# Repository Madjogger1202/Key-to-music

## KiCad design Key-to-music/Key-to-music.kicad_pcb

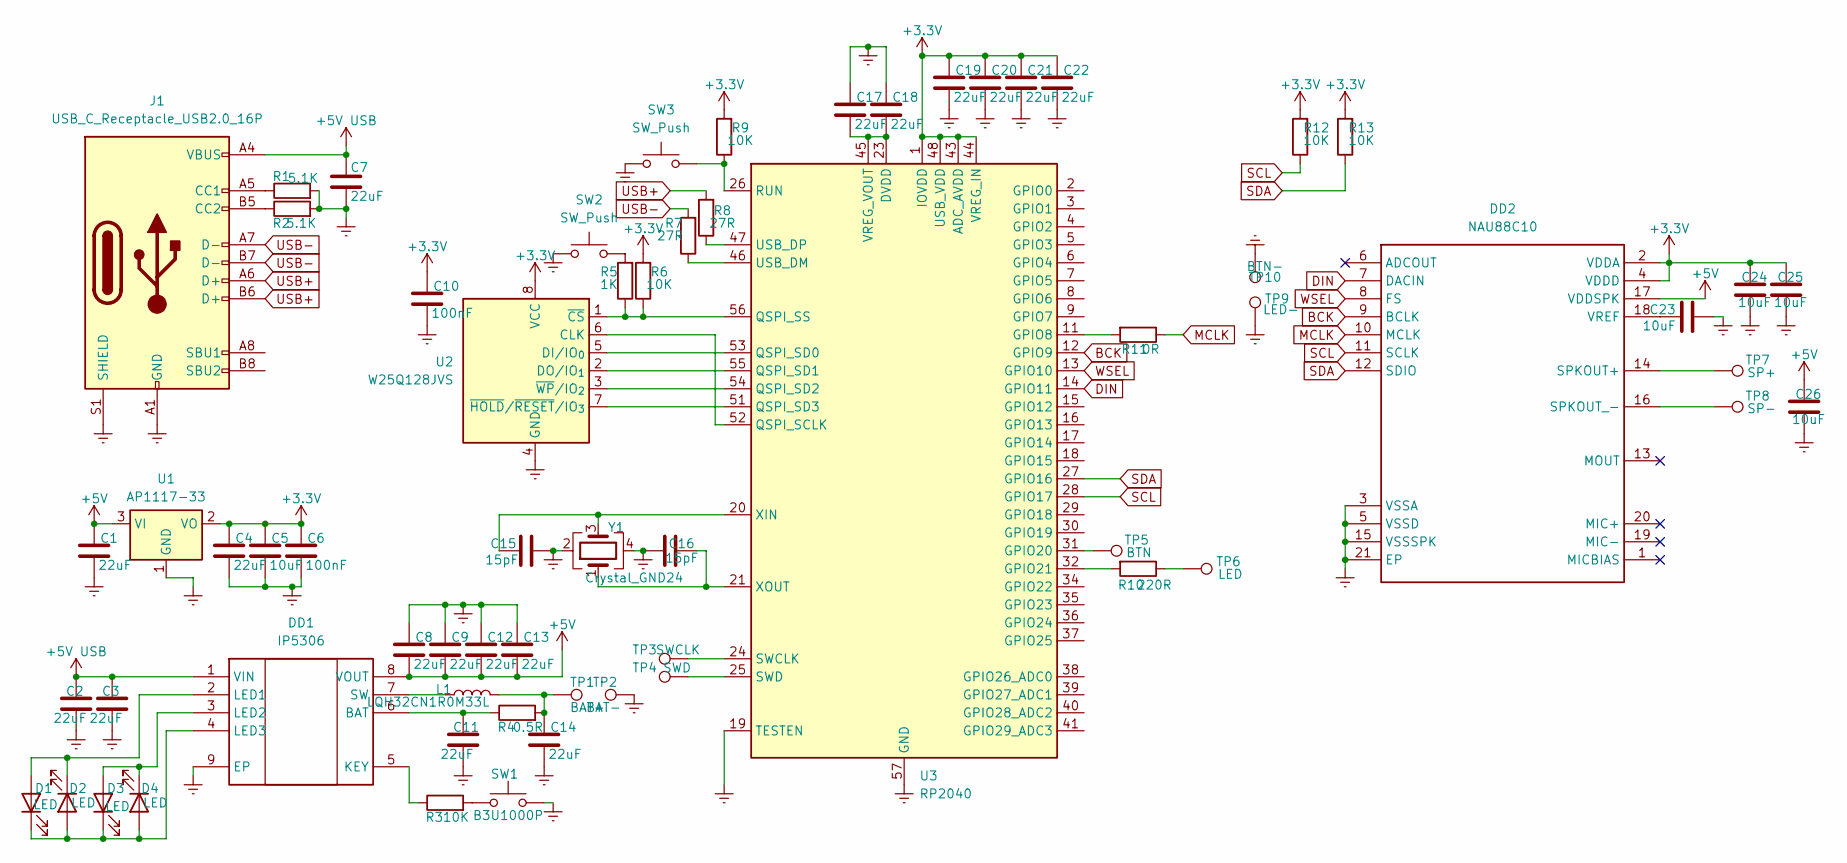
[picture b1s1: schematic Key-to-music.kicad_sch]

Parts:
C1, C2, C3, C4, C7, C8, C9, C11, C12, C13, C14, C17, C18, C19, C20, C21, C22: 22uF; C_0402_1005Metric
C5, C23, C24, C25, C26: 10uF; C_0402_1005Metric
C6, C10: 100nF; C_0402_1005Metric
C15, C16: 15pF; C_0402_1005Metric
D1, D2, D3, D4: LED; LED_0402_1005Metric
DD1: IP5306; HSOP-8-1EP_3.9x4.9mm_P1.27mm_EP2.3x2.3mm; Manufacturer_Part_Number IP5306
DD2: NAU88C10; QFN50P400X400X80-21N; Manufacturer_Part_Number NAU88C10
J1: USB_C_Receptacle_USB2.0_16P; USB_C_Receptacle_GCT_USB4105-xx-A_16P_TopMnt_Horizontal
L1: LQH32CN1R0M33L; L_1210_3225Metric
R1, R2: 5.1K; R_0402_1005Metric
R3, R6, R9, R12, R13: 10K; R_0402_1005Metric
R4: 0.5R; R_0402_1005Metric
R5: 1K; R_0402_1005Metric
R7, R8: 27R; R_0402_1005Metric
R10: 220R; R_0402_1005Metric
R11: 0R; R_0402_1005Metric
SW1: B3U1000P; SW_SPST_B3U-1000P
SW2, SW3: SW_Push; SW_SPST_B3U-1000P
TP1: BAT+; TestPoint_Pad_D2.0mm
TP2: BAT-; TestPoint_Pad_D2.0mm
TP3: SWCLK; TestPoint_Pad_D1.0mm
TP4: SWD; TestPoint_Pad_D1.0mm
TP5: BTN; TestPoint_Pad_D1.0mm
TP6: LED; TestPoint_Pad_D1.0mm
TP7: SP+; TestPoint_Pad_D1.0mm
TP8: SP-; TestPoint_Pad_D1.0mm
TP9: LED-; TestPoint_Pad_D1.0mm
TP10: BTN-; TestPoint_Pad_D1.0mm
U1: AP1117-33; SOT-223-3_TabPin2
U2: W25Q128JVS; SOIC-8_5.3x5.3mm_P1.27mm
U3: RP2040; QFN-56-1EP_7x7mm_P0.4mm_EP3.2x3.2mm
Y1: Crystal_GND24; Crystal_SMD_Abracon_ABM8G-4Pin_3.2x2.5mm

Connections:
+3.3V: C4.1, C5.1, C6.1, C10.1, C19.1, C20.1, C21.1, C22.1, C24.2, C25.2, DD2.2 (VDDA), DD2.4 (VDDD), R6.2, R9.2, R12.2, R13.2, U1.2 (VO), U2.8 (VCC), U3.1 (IOVDD), U3.10 (IOVDD), U3.22 (IOVDD), U3.33 (IOVDD), U3.42 (IOVDD), U3.43 (ADC_AVDD), U3.44 (VREG_IN), U3.48 (USB_VDD), U3.49 (IOVDD)
+5V: C1.1, C8.2, C9.2, C12.2, C13.2, C26.2, DD1.8 (VOUT), DD2.17 (VDDSPK), U1.3 (VI)
+5V USB: C2.1, C3.1, C7.1, DD1.1 (VIN), J1.A4 (VBUS), J1.A9 (VBUS), J1.B4 (VBUS), J1.B9 (VBUS)
BCK: DD2.9 (BCLK), U3.12 (GPIO9)
DIN: DD2.7 (DACIN), U3.14 (GPIO11)
Earth: C1.2, C2.2, C3.2, C4.2, C5.2, C6.2, C7.2, C8.1, C9.1, C10.2, C11.2, C12.1, C13.1, C14.2, C15.2, C16.1, C17.1, C18.1, C19.2, C20.2, C21.2, C22.2, C23.2, C24.1, C25.1, C26.1, DD1.9 (EP), DD2.3 (VSSA), DD2.5 (VSSD), DD2.15 (VSSSPK), DD2.21 (EP), J1.A1 (GND), J1.A12 (GND), J1.B1 (GND), J1.B12 (GND), J1.S1 (SHIELD), R1.2, R2.2, SW1.2, SW2.1, SW3.1, TP2.1, TP9.1, TP10.1, U1.1 (GND), U2.4 (GND), U3.19 (TESTEN), U3.57 (GND), Y1.2, Y1.4
MCLK: DD2.10 (MCLK), R11.1
unnamed: C14.1, L1.2, R4.2, TP1.1
unnamed: D1.2 (A), D2.1 (K), DD1.2 (LED1)
unnamed: D1.1 (K), D2.2 (A), D3.1 (K), D4.2 (A), DD1.4 (LED3)
unnamed: D3.2 (A), D4.1 (K), DD1.3 (LED2)
unnamed: C11.1, DD1.6 (BAT), R4.1
unnamed: DD1.5 (KEY), R3.1
unnamed: DD1.7 (SW), L1.1
unnamed: DD2.14 (SPKOUT+), TP7.1
unnamed: DD2.16 (SPKOUT_-), TP8.1
unnamed: C23.1, DD2.18 (VREF)
unnamed: J1.A5 (CC1), R1.1
unnamed: J1.B5 (CC2), R2.1
unnamed: R3.2, SW1.1
unnamed: R5.2, SW2.2
unnamed: R10.1, TP6.1
unnamed: U2.6 (CLK), U3.52 (QSPI_SCLK)
unnamed: U2.5 (DI/IO_{0}), U3.53 (QSPI_SD0)
unnamed: U2.2 (DO/IO_{1}), U3.55 (QSPI_SD1)
unnamed: R5.1, R6.1, U2.1 (~CS), U3.56 (QSPI_SS)
unnamed: U2.7 (~HOLD/~RESET/IO_{3}), U3.51 (QSPI_SD3)
unnamed: U2.3 (~WP/IO_{2}), U3.54 (QSPI_SD2)
unnamed: R11.2, U3.11 (GPIO8)
unnamed: TP5.1, U3.31 (GPIO20)
unnamed: R10.2, U3.32 (GPIO21)
unnamed: R9.1, SW3.2, U3.26 (RUN)
unnamed: TP3.1, U3.24 (SWCLK)
unnamed: TP4.1, U3.25 (SWD)
unnamed: R7.1, U3.46 (USB_DM)
unnamed: R8.1, U3.47 (USB_DP)
unnamed: C17.2, C18.2, U3.23 (DVDD), U3.45 (VREG_VOUT), U3.50 (DVDD)
unnamed: C15.1, U3.20 (XIN), Y1.3
unnamed: C16.2, U3.21 (XOUT), Y1.1
SCL: DD2.11 (SCLK), R12.1, U3.28 (GPIO17)
SDA: DD2.12 (SDIO), R13.1, U3.27 (GPIO16)
USB+: J1.A6 (D+), J1.B6 (D+), R8.2
USB-: J1.A7 (D-), J1.B7 (D-), R7.2
WSEL: DD2.8 (FS), U3.13 (GPIO10)

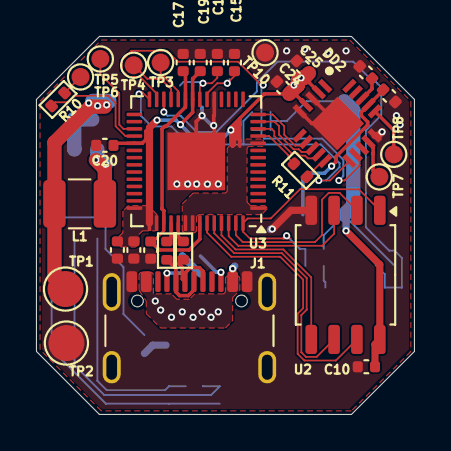
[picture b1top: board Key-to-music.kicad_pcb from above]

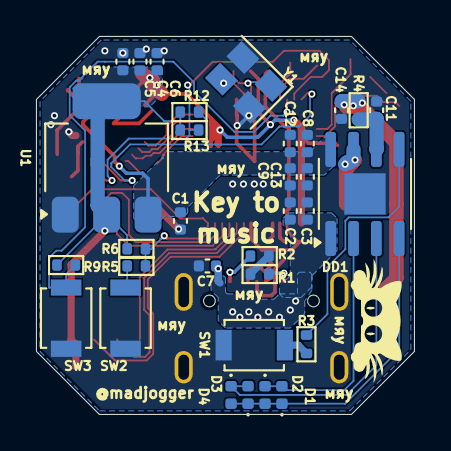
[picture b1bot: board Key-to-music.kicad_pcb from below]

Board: 2 copper layers, 21.0 x 21.0 mm, 63 parts (32 on the bottom side), 44 nets.

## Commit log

2025-04-14 Созданы компоненты, подготовлен набросок схемы
2025-04-17 Завершена схема и сделана компоновка
2025-04-18 rev0 готова
